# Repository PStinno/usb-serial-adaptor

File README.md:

# USB Serial Adaptor
Simple USB to UART adaptor using the low cost CH340 IC.

The board features a Micro USB B connector for connection to a computer and a six pin 0.1 inch pitch header, with a connection scheme matching that of several existing USB serial boards and cables. The power and signal voltage of the UART connection is selectable between 5V and 3.3V via a header on the rear of the board. 3.3V is supplied by an onboard LDO which regulates down the 5V from the USB connection. Indicator LEDs for RX and TX activity are also included.

[![CC BY-SA 4.0][cc-by-sa-image]][cc-by-sa]

[cc-by-sa]: http://creativecommons.org/licenses/by-sa/4.0/
[cc-by-sa-image]: https://licensebuttons.net/l/by-sa/4.0/88x31.png
[cc-by-sa-shield]: https://img.shields.io/badge/License-CC%20BY--SA%204.0-lightgrey.svg

This work is licensed under a [Creative Commons Attribution-ShareAlike 4.0 International License][cc-by-sa].

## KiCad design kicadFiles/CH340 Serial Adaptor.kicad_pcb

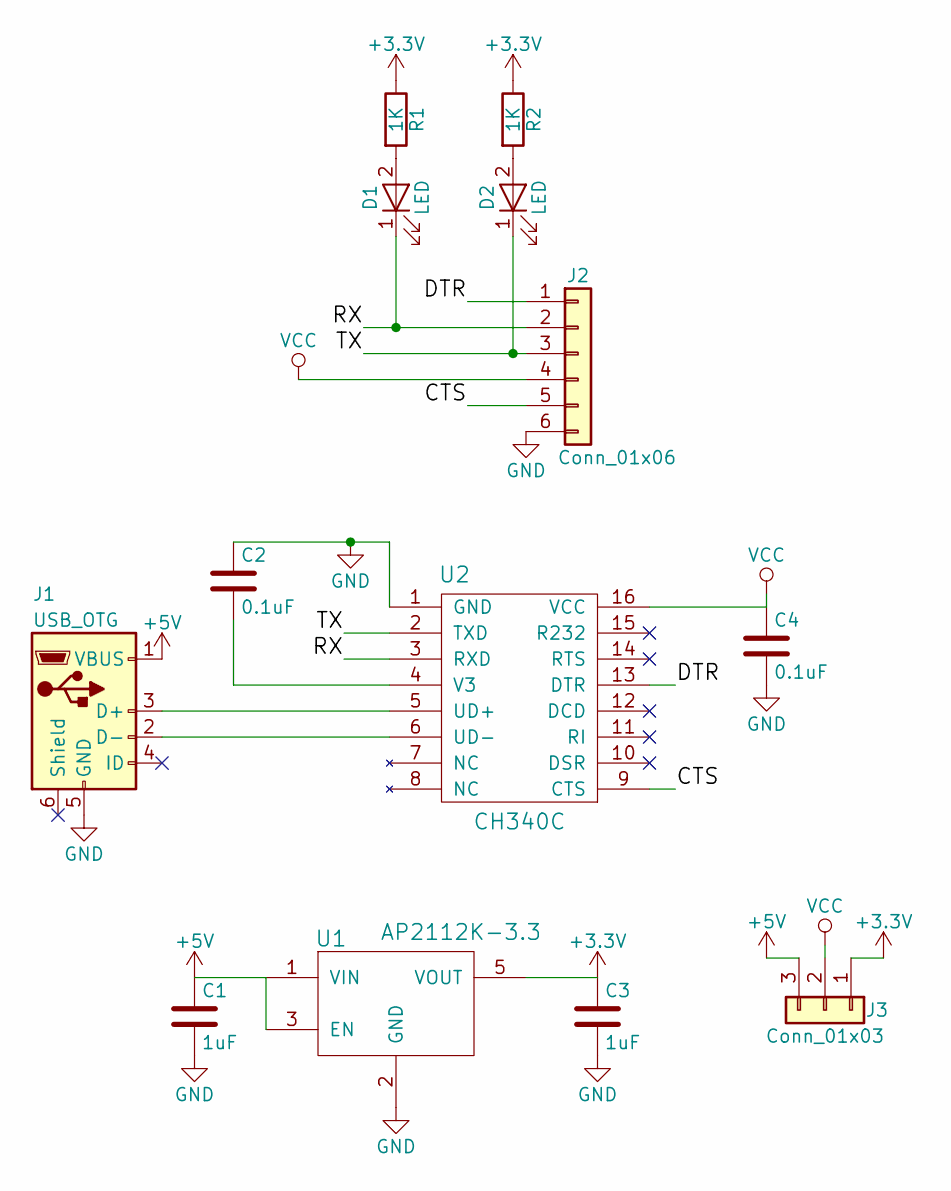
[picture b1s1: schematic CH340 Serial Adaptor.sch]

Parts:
C1, C3: 1uF; C_0603
C2, C4: 0.1uF; C_0603
D1, D2: LED; LED_0805
J1: USB_OTG; Amphenol_10118194-0001LF_Micro_USB_B
J2: Conn_01x06; Harwin_0.1_6POS_SMD_RA
J3: Conn_01x03; HARWIN_SMD_RA_3POS
R1, R2: 1K; R_0603
U1: AP2112K-3.3; SOT-23-5
U2: CH340C; SOIC-16_3.9x9.9mm_Pitch1.27mm

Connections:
+3V3: C3.1, J3.1, R1.1, R2.1, U1.5 (VOUT)
+5V: C1.1, J1.1 (VBUS), J3.3, U1.1 (VIN), U1.3 (EN)
/CTS: J2.5, U2.9 (CTS)
/DTR: J2.1, U2.13 (DTR)
/RX: D1.1 (K), J2.2, U2.3 (RXD)
/TX: D2.1 (K), J2.3, U2.2 (TXD)
GND: C1.2, C2.1, C3.2, C4.2, J1.5 (GND), J2.6, U1.2 (GND), U2.1 (GND)
unnamed: C2.2, U2.4 (V3)
unnamed: D1.2 (A), R1.2
unnamed: D2.2 (A), R2.2
unnamed: J1.2 (D-), U2.6 (UD-)
unnamed: J1.3 (D+), U2.5 (UD+)
VCC: C4.1, J2.4, J3.2, U2.16 (VCC)

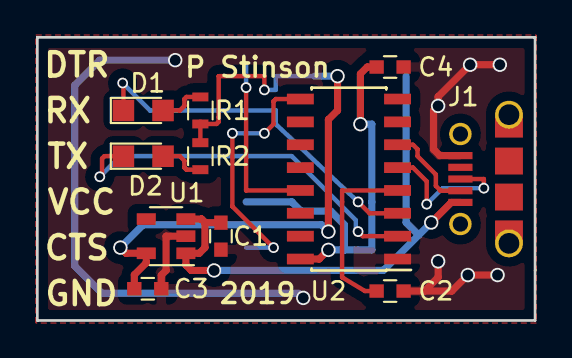
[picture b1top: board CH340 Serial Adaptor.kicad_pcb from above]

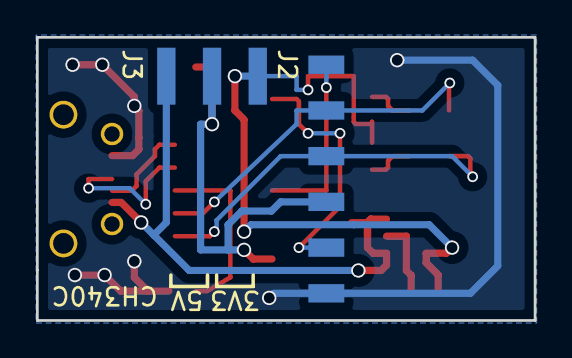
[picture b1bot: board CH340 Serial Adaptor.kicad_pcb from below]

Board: 2 copper layers, 27.7 x 15.7 mm, 13 parts (2 on the bottom side), 13 nets.

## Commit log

2020-03-29 Add project images.
2020-03-29 Add Kicad design files.
2022-04-14 Added license file
